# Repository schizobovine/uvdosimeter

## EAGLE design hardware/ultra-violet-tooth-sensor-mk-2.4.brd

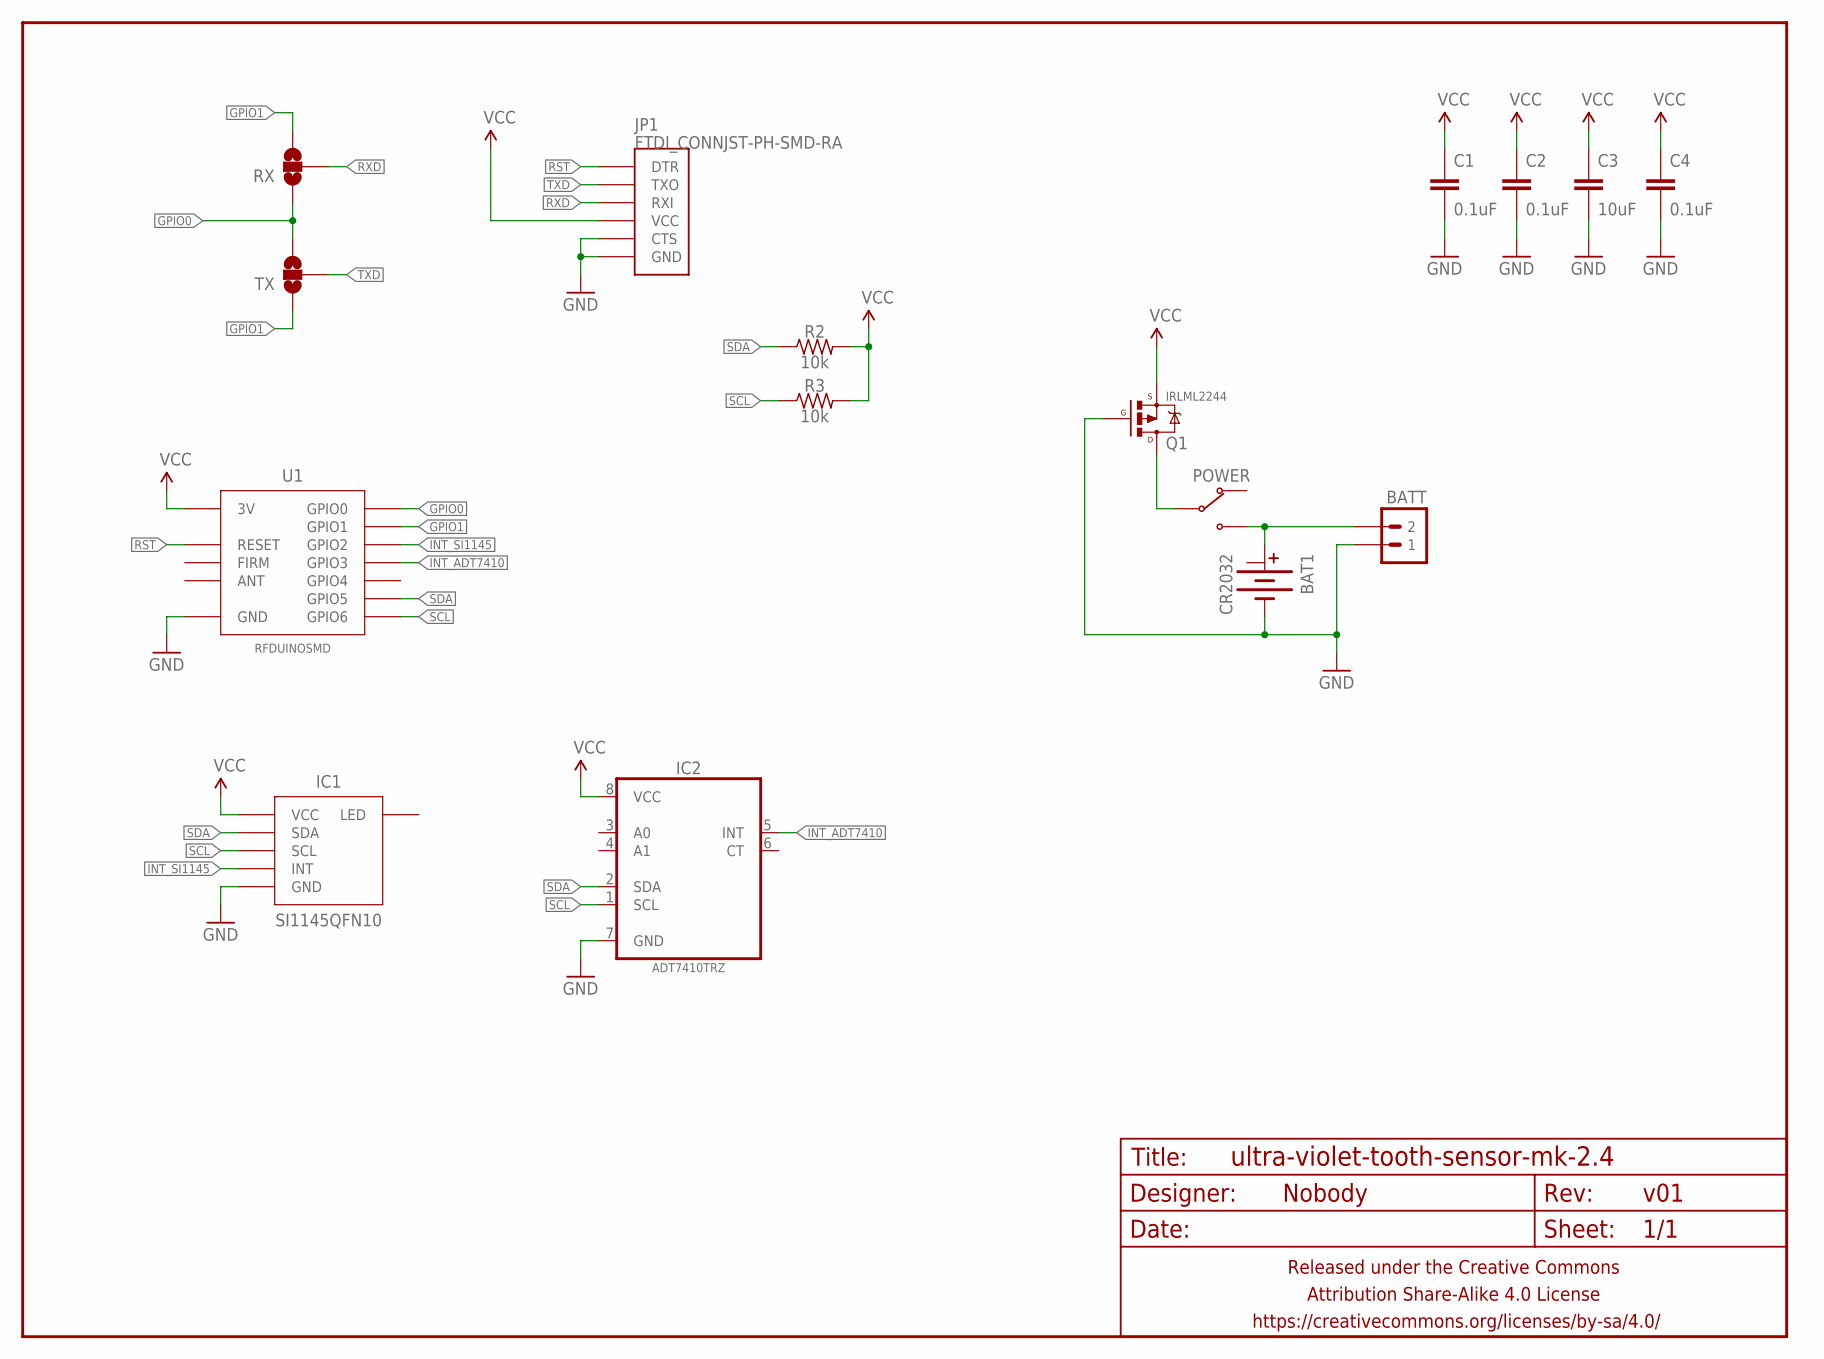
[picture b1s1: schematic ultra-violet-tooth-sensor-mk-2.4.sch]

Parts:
BAT1: CR2032; BATTCON_20MM_MINE_STAHPIT
BATT: M02PTH-CENTERED-R+; 1X02-CENTER-R+
C1: 0.1uF; C0805
C2, C4: 0.1uF; C0603
C3: 10uF; C1206
FRAME1: FRAME-LETTERNO_PACKAGE; DUMMY
IC1: SI1145QFN10; SI1145
IC2: ADT7410TRZ; SOIC127P600X175-8N
JP1: FTDI_CONNJST-PH-SMD-RA; AVRISP-JST-6-PH-RA-SMD
POWER: SWITCH-SPDTPTH-RA-2.54MM; SPDT-RA-2.54MM
Q1: IRLML2244; SOT23-3
R2, R3: 10k; R0603
RX: JUMPER-PAD-3-NOFULL_BOX_SILK; PAD-JUMPER-3-NO_YES_SILK_FULL_BOX
TX: JUMPER-PAD-3-NOFULL_BOX_SILK; PAD-JUMPER-3-NO_YES_SILK_FULL_BOX
U1: RFDUINOSMD; RFDUINO-SMD

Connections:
GND: BAT1.BOTTOM (-), BATT.1, C1.2, C2.2, C3.2, C4.2, IC1.GND, IC2.7 (GND), JP1.CTS, JP1.GND, Q1.1 (G), U1.GND@1 (GND), U1.GND@2 (GND), U1.GND@3 (GND), U1.GND@4 (GND), U1.GND@5 (GND), U1.GND@6 (GND), U1.GND@7 (GND), U1.GND@8 (GND)
GPIO0: RX.1, TX.3, U1.GPIO0
GPIO1: RX.3, TX.1, U1.GPIO1
INT_ADT7410: IC2.5 (INT), U1.GPIO3
INT_SI1145: IC1.INT, U1.GPIO2
unnamed: BAT1.TOP@1 (+), BATT.2, POWER.3 (NO)
unnamed: POWER.2 (COM), Q1.3 (D)
RST: JP1.DTR, U1.RESET
RXD: JP1.RXI, RX.2
SCL: IC1.SCL, IC2.1 (SCL), R3.1, U1.GPIO6
SDA: IC1.SDA, IC2.2 (SDA), R2.1, U1.GPIO5
TXD: JP1.TXO, TX.2
VCC: C1.1, C2.1, C3.1, C4.1, IC1.VCC@1 (VCC), IC1.VCC@2 (VCC), IC1.VCC@3 (VCC), IC2.8 (VCC), JP1.VCC, Q1.2 (S), R2.2, R3.2, U1.3V

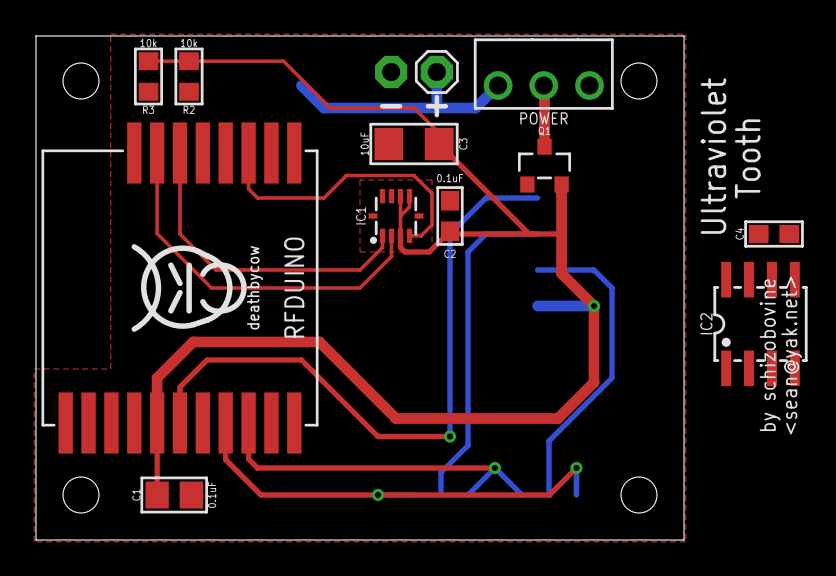
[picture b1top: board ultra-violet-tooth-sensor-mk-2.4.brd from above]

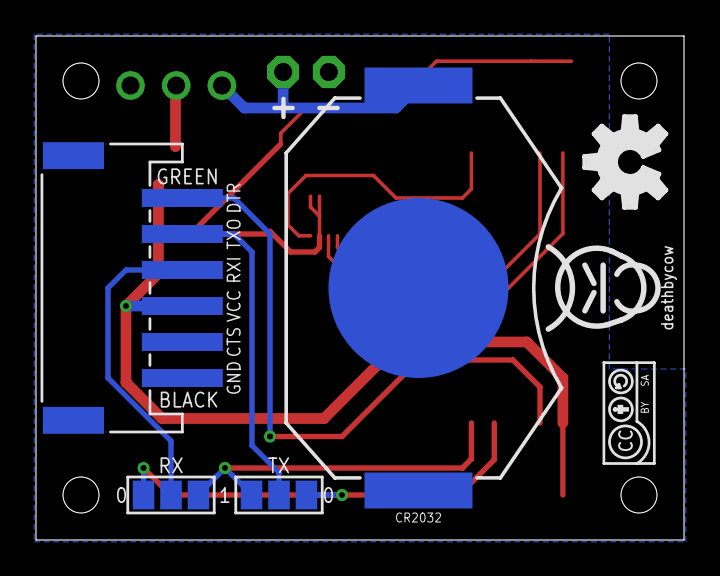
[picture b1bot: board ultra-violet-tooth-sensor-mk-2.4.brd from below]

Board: 2 copper layers, 36.0 x 28.0 mm, 21 parts (7 on the bottom side), 13 nets.

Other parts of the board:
U$1: CC-BY-SA-4.0-NO-URL
U$2, U$5: COW_SMALL
U$6: OSHWLOGO_SILKONLY

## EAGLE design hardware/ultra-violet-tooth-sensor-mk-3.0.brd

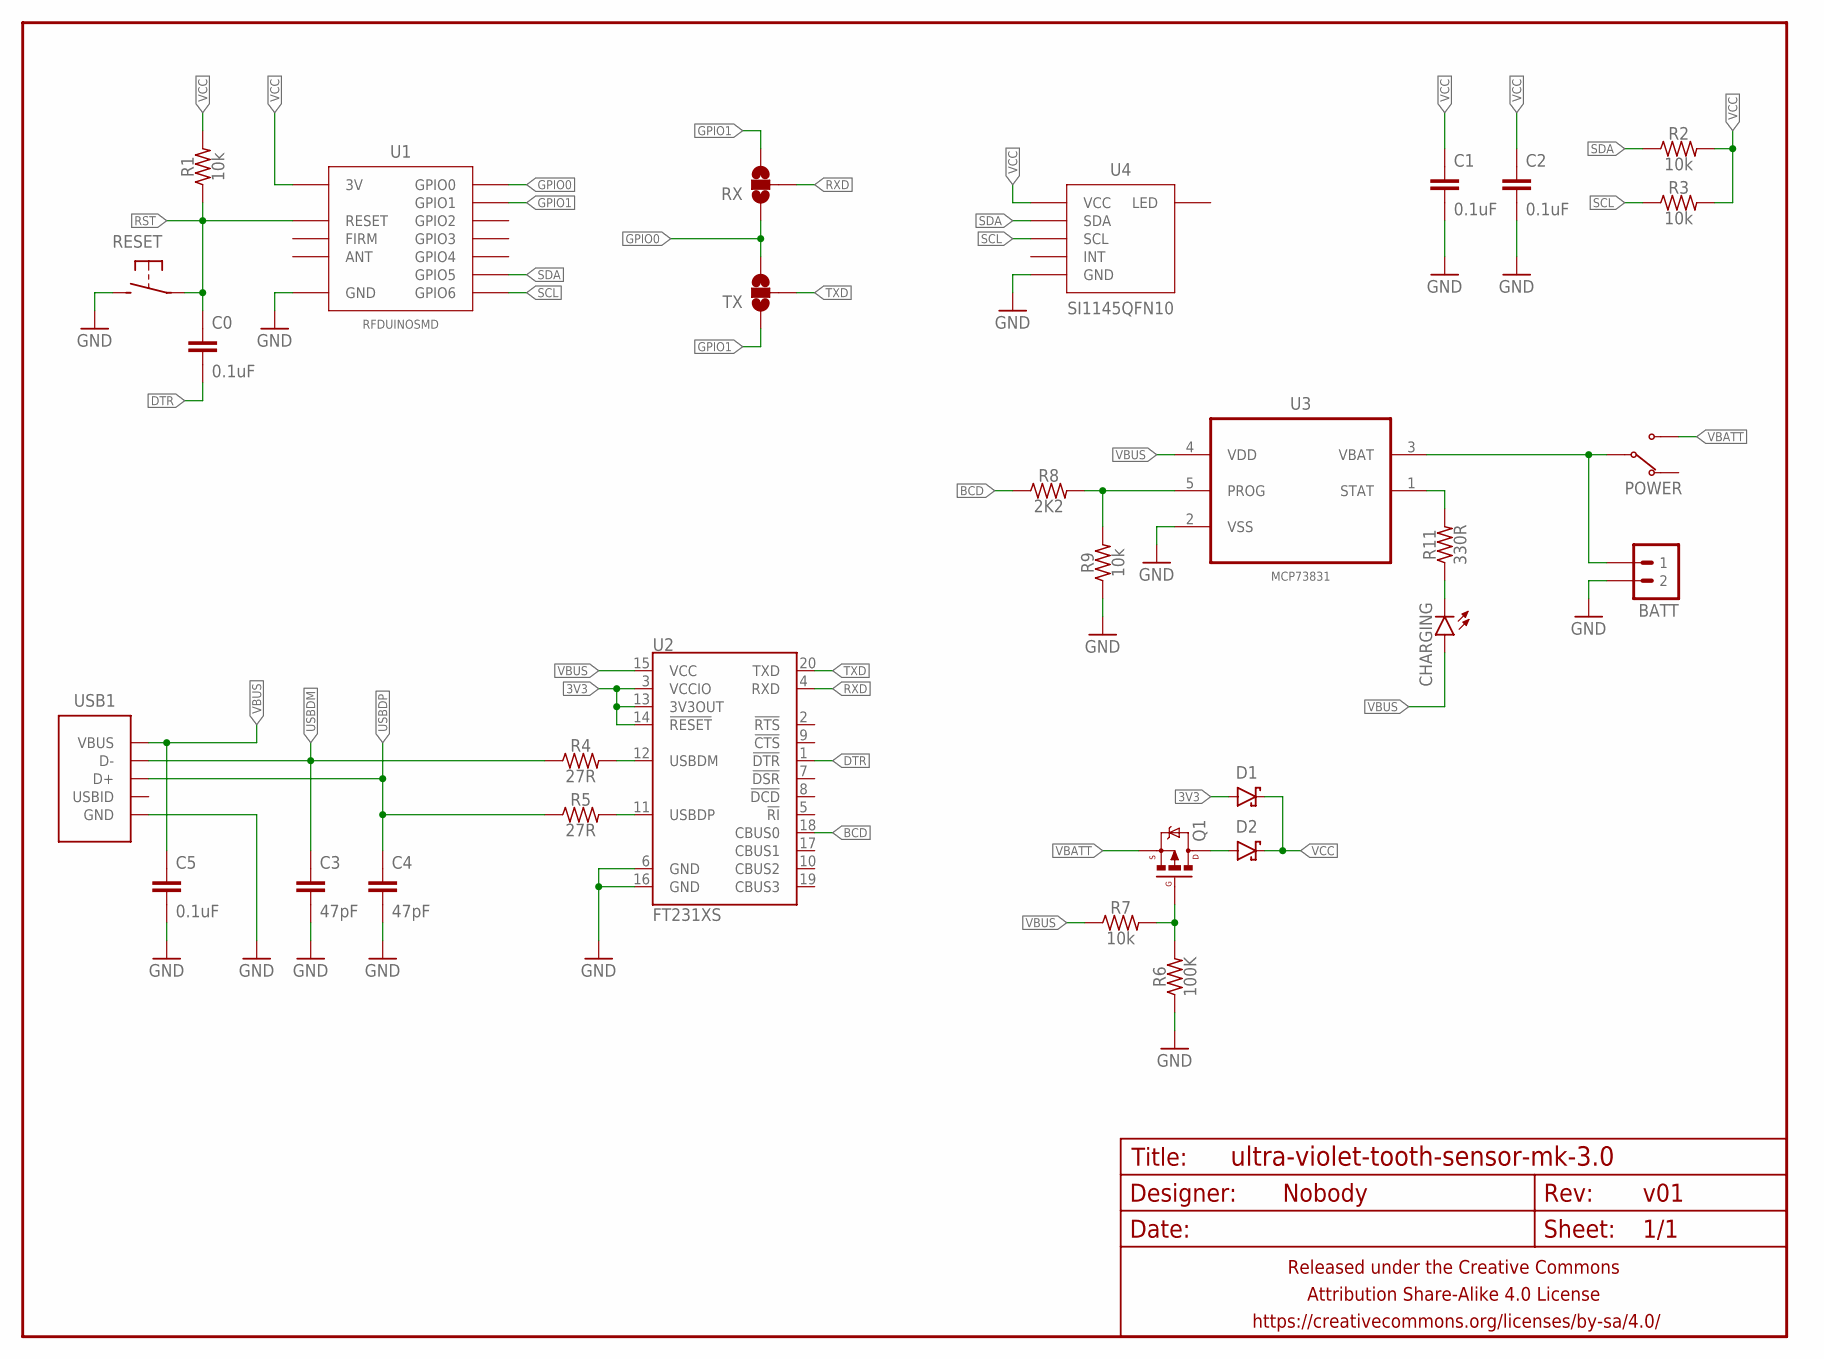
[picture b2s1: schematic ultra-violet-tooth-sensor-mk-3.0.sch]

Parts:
BATT: M02JST-2MM-SMT; JST-2-SMD
C0, C1, C2, C5: 0.1uF; C0603
C3, C4: 47pF; C0603
CHARGING: LED1206; LED-1206
D1, D2: DIODE-SCHOTTKYSMA; SMA-DIODE-SCHOTTKY
FRAME1: FRAME-LETTERNO_PACKAGE; DUMMY
POWER: SWITCH-SPDTPTH-RA-2.54MM; SPDT-RA-2.54MM
Q1: MOSFET-PCHANNELIRLML2244; SOT23-3
R1, R2, R3, R7, R9: 10k; R0603
R4, R5: 27R; R0603
R6: 100K; R0603
R8: 2K2; R0603
R11: 330R; R0603
RESET: SPST-NO-TACT3MM-RA; TACTILE-PTH-SIDE
RX: JUMPER-PAD-3-NOFULL_BOX_SILK; PAD-JUMPER-3-NO_YES_SILK_FULL_BOX
TX: JUMPER-PAD-3-NOFULL_BOX_SILK; PAD-JUMPER-3-NO_YES_SILK_FULL_BOX
U1: RFDUINOSMD; RFDUINO-SMD
U2: FT231XS; SSOP20_L
U3: MCP73831; SOT95P280X145-5N
U4: SI1145QFN10; SI1145
USB1: USB-ABCOMBO; USB-MICRO-B-FCI-CUTOUT

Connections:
3V3: D1.A, U2.3 (VCCIO), U2.13 (3V3OUT), U2.14 (!RESET)
BCD: R8.1, U2.18 (CBUS0)
DTR: C0.2, U2.1 (!DTR)
GND: BATT.1 (2), C1.2, C2.2, C3.2, C4.2, C5.2, R6.1, R9.1, RESET.2, U1.GND@1 (GND), U1.GND@2 (GND), U1.GND@3 (GND), U1.GND@4 (GND), U1.GND@5 (GND), U1.GND@6 (GND), U1.GND@7 (GND), U1.GND@8 (GND), U2.6 (GND), U2.16 (GND), U3.2 (VSS), U4.GND, USB1.5 (GND), USB1.P$1 (GND), USB1.P$2 (GND)
GPIO0: RX.1, TX.3, U1.GPIO0
GPIO1: RX.3, TX.1, U1.GPIO1
unnamed: Q1.1 (G), R6.2, R7.2
unnamed: BATT.2 (1), POWER.2 (COM), U3.3 (VBAT)
unnamed: R11.2, U3.1 (STAT)
unnamed: CHARGING.C, R11.1
unnamed: D2.A, Q1.3 (D)
unnamed: R4.2, U2.12 (USBDM)
unnamed: R5.2, U2.11 (USBDP)
PROG: R8.2, R9.2, U3.5 (PROG)
RST: C0.1, R1.1, RESET.1, U1.RESET
RXD: RX.2, U2.4 (RXD)
SCL: R3.1, U1.GPIO6, U4.SCL
SDA: R2.1, U1.GPIO5, U4.SDA
TXD: TX.2, U2.20 (TXD)
USBDM: C3.1, R4.1, USB1.2 (D-)
USBDP: C4.1, R5.1, USB1.3 (D+)
VBATT: POWER.3 (NO), Q1.2 (S)
VBUS: C5.1, CHARGING.A, R7.1, U2.15 (VCC), U3.4 (VDD), USB1.1 (VBUS)
VCC: C1.1, C2.1, D1.C, D2.C, R1.2, R2.2, R3.2, U1.3V, U4.VCC@1 (VCC), U4.VCC@2 (VCC), U4.VCC@3 (VCC)

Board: 2 copper layers, 33 parts (11 on the bottom side), 24 nets, no tracks yet.

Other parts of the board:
U$1: CC-BY-SA-4.0-NO-URL
U$3: OSHWLOGO_TOP_0.2

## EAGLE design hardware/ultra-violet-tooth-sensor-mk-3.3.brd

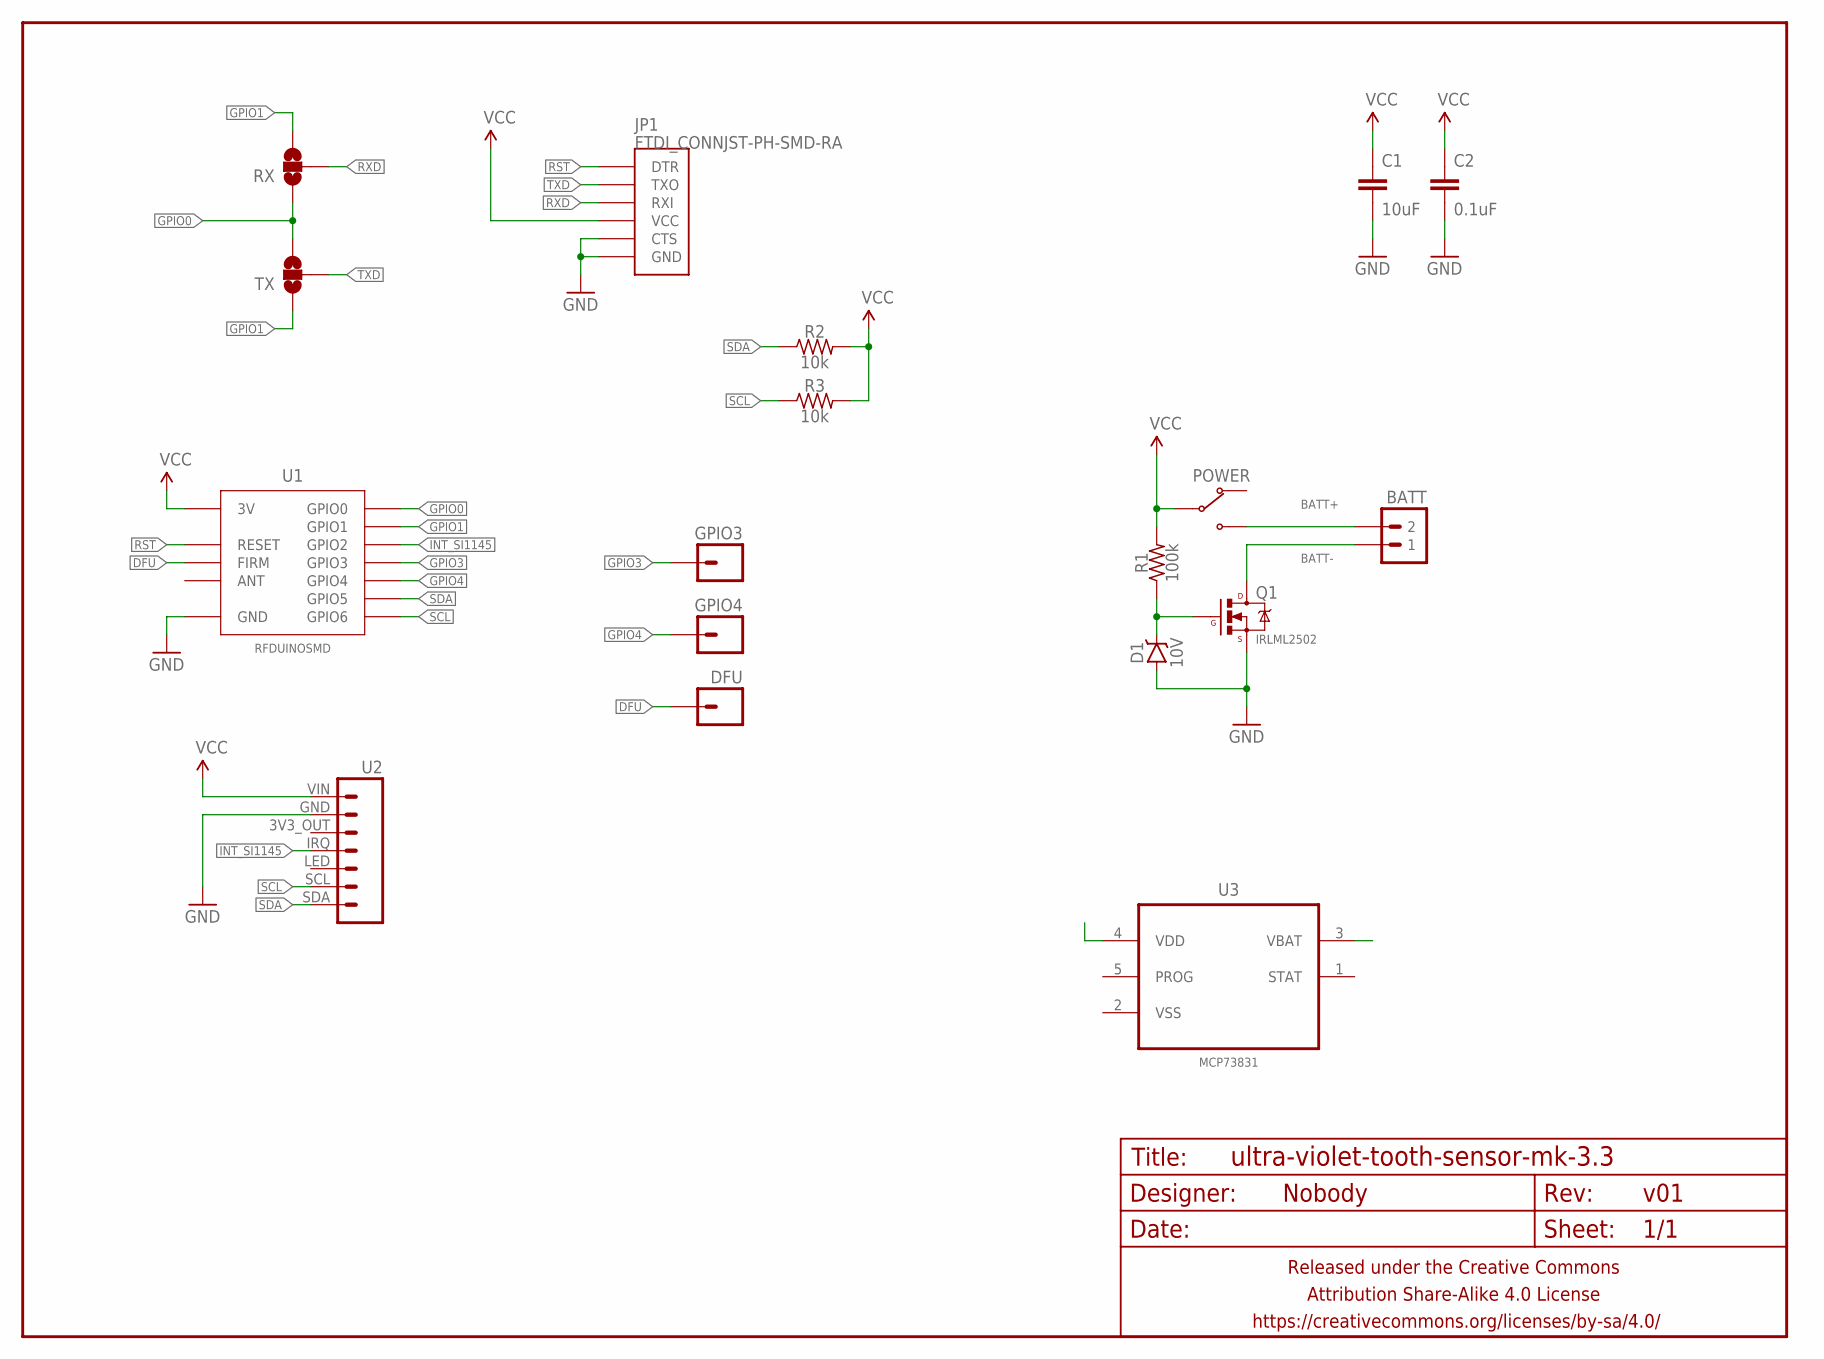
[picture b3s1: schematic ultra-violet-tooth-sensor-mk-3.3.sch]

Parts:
BATT: M02PTH-CENTERED-R+; 1X02-CENTER-R+
C1: 10uF; C1206
C2: 0.1uF; C0805
D1: 10V; SOT23
DFU: M01SMD_1.5X2MM; 1X01_1.5X2MM
FRAME1: FRAME-LETTERNO_PACKAGE; DUMMY
GPIO3, GPIO4: M01SMD_1.5X2MM; 1X01_1.5X2MM
JP1: FTDI_CONNJST-PH-SMD-RA; AVRISP-JST-6-PH-RA-SMD
POWER: SWITCH-SPDTPTH-RA-2.54MM; SPDT-RA-2.54MM
Q1: IRLML2502; SOT23
R1: 100k; R0805
R2, R3: 10k; R0805
RX: JUMPER-PAD-3-NOFULL_BOX_SILK; PAD-JUMPER-3-NO_YES_SILK_FULL_BOX
TX: JUMPER-PAD-3-NOFULL_BOX_SILK; PAD-JUMPER-3-NO_YES_SILK_FULL_BOX
U1: RFDUINOSMD; RFDUINO-SMD
U2: ADAFRUIT-SI1145-BREAKOUTNOHOLEY; ADAFRUIT-SI1145-BREAKOUT-NOHOLES
U3: MCP73831; SOT95P280X145-5N

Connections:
BATT+: BATT.2, POWER.3 (NO)
BATT-: BATT.1, Q1.3 (D)
DFU: DFU.P$1, U1.FACTORY (FIRM)
GND: C1.2, C2.2, D1.1 (A), D1.2 (A), JP1.CTS, JP1.GND, Q1.2 (S), U1.GND@1 (GND), U1.GND@2 (GND), U1.GND@3 (GND), U1.GND@4 (GND), U1.GND@5 (GND), U1.GND@6 (GND), U1.GND@7 (GND), U1.GND@8 (GND), U2.GND
GPIO0: RX.1, TX.3, U1.GPIO0
GPIO1: RX.3, TX.1, U1.GPIO1
GPIO3: GPIO3.P$1, U1.GPIO3
GPIO4: GPIO4.P$1, U1.GPIO4
INT_SI1145: U1.GPIO2, U2.IRQ
unnamed: D1.3 (C), Q1.1 (G), R1.1
RST: JP1.DTR, U1.RESET
RXD: JP1.RXI, RX.2
SCL: R3.1, U1.GPIO6, U2.SCL
SDA: R2.1, U1.GPIO5, U2.SDA
TXD: JP1.TXO, TX.2
VCC: C1.1, C2.1, JP1.VCC, POWER.2 (COM), R1.2, R2.2, R3.2, U1.3V, U2.VIN
VSS: U3.2 (VSS)

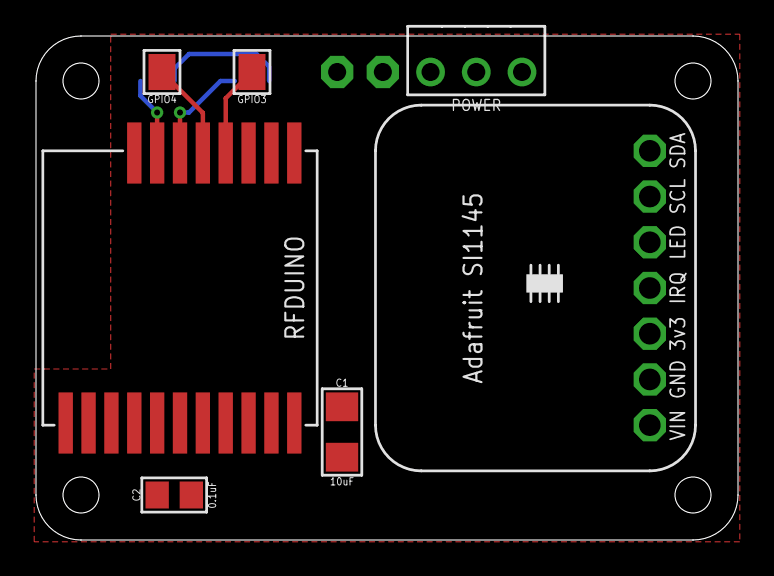
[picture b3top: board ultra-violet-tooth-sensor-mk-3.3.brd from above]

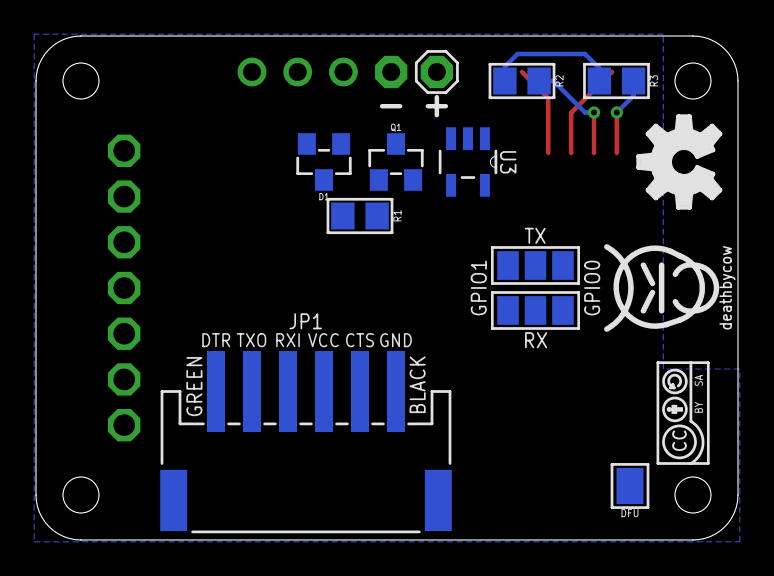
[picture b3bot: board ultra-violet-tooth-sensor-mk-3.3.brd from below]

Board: 2 copper layers, 39.0 x 28.0 mm, 22 parts (14 on the bottom side), 16 nets.

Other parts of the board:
U$1: CC-BY-SA-4.0-NO-URL
U$2: COW_SMALL
U$6: OSHWLOGO_SILKONLY

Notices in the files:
parts and their libraries:
A_butts: Released under the Creative Commons Attribution Share-Alike 4.0 License
A_butts: https://creativecommons.org/licenses/by-sa/4.0
A_butts: Released under the Creative Commons
